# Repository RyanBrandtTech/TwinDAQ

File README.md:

# TwinDAQ
* An STM32-based two-channel analog I/O data acquisition system and development board

## Features
* Two analog inputs accessible with SMA connectors
* Two analog outputs accessible with SMA connectors
* Eight digital GPIO accessible via 0.1" female pin headers
* Two RGB LEDs for visual debugging
* Connector for SWD interfacing
* Connector for UART interfacing
* Micro-USB for 5V power and USB2.0 communications

### Dimensions and Images
40 mm x 60 mm

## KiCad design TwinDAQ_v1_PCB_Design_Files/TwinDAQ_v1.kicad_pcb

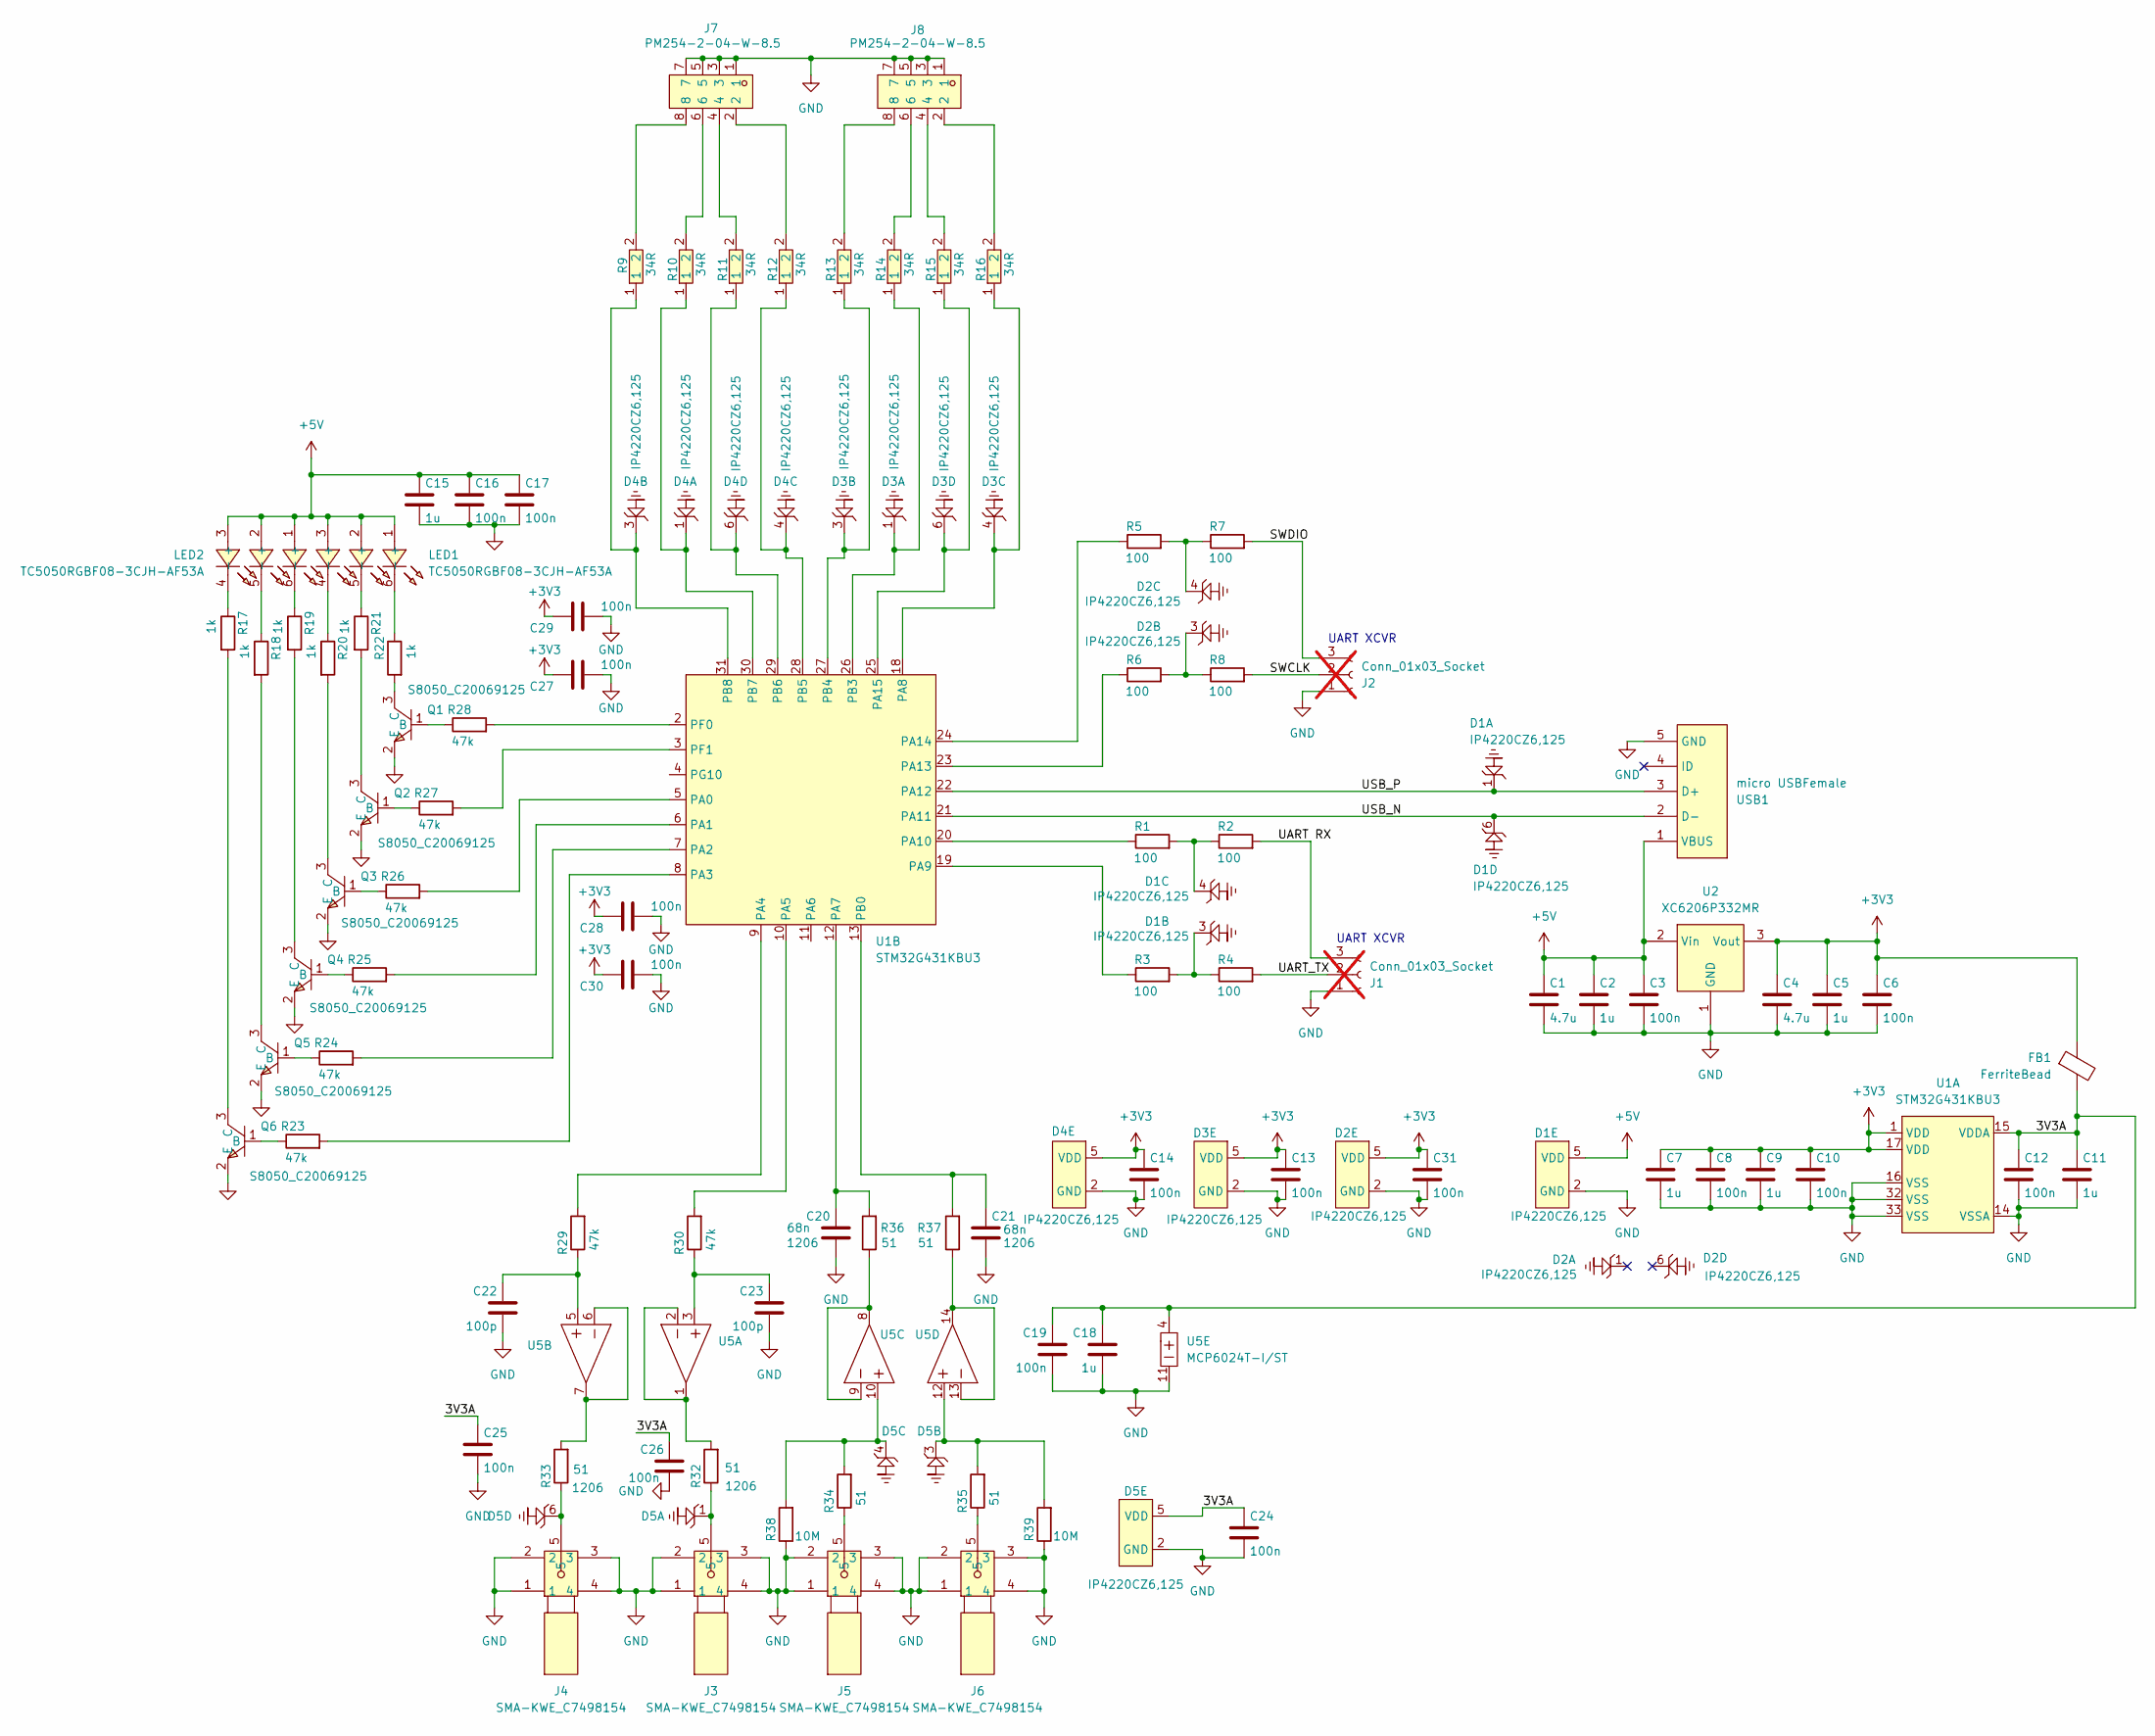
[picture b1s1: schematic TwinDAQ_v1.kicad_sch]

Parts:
C1, C4: 4.7u; C_0402_1005Metric_Pad0.74x0.62mm_HandSolder; LCSC Part C23733
C2, C5, C7, C9, C11, C15, C18: 1u; C_0402_1005Metric_Pad0.74x0.62mm_HandSolder; LCSC Part C14445
C3, C6, C8, C10, C12, C13, C14, C16, C17, C19, C24, C25, C26, C27, C28, C29, C30, C31: 100n; C_0402_1005Metric_Pad0.74x0.62mm_HandSolder; LCSC Part C1525
C20, C21: 68n; C1206; LCSC Part C77084
C22, C23: 100p; C0402; LCSC Part C1546
D1, D2, D3, D4, D5: IP4220CZ6,125; TSOP-6_L3.0-W1.5-P0.95-LS2.8-BR; LCSC Part C282546
FB1: FerriteBead; L_0603_1608Metric_Pad1.05x0.95mm_HandSolder; LCSC Part C1002
J1, J2: Conn_01x03_Socket; PinSocket_1x03_P2.54mm_Vertical; LCSC Part C541850; not fitted
J3, J4, J5, J6: SMA-KWE_C7498154; SMA-TH_SMA-KWE_C7498154; LCSC Part C7498154
J7, J8: PM254-2-04-W-8.5; HDR-TH_8P-P2.54-H-F-R2-C4-W8.5; LCSC Part C2897424
LED1, LED2: TC5050RGBF08-3CJH-AF53A; LED-SMD_6P-L5.0-W5.0-TL_TC5050RGBF08; LCSC Part C784540
Q1, Q2, Q3, Q4, Q5, Q6: S8050_C20069125; SOT-23-3_L2.9-W1.3-P1.90-LS2.3-BR; LCSC Part C20069125
R1, R2, R3, R4, R5, R6, R7, R8: 100; R_0402_1005Metric_Pad0.72x0.64mm_HandSolder; LCSC Part C25076
R9, R10, R11, R12, R13, R14, R15, R16: 34R; R0603; LCSC Part C25193
R17, R18, R19, R20, R21, R22: 1k; R0402; LCSC Part C11702
R23, R24, R25, R26, R27, R28, R29, R30: 47k; R0402; LCSC Part C25792
R32, R33: 51; R1206; LCSC Part C18019
R34, R35, R36, R37: 51; R0402; LCSC Part C25125
R38, R39: 10M; R0402; LCSC Part C26082
U1: STM32G431KBU3; QFN-32-1EP_5x5mm_P0.5mm_EP3.45x3.45mm; LCSC Part C1341901
U2: XC6206P332MR; SOT-23-3_L2.9-W1.6-P1.90-LS2.8-BR; LCSC Part C5446
U5: MCP6024T-I/ST; TSSOP-14_L5.0-W4.4-P0.65-LS6.5-BL; LCSC Part C480630
USB1: micro USBFemale; MICRO-USB-SMD_5P-P0.65-H-F_C10418; LCSC Part C10418

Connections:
+3V3: C4.1, C5.1, C6.1, C7.1, C8.1, C9.1, C10.1, C13.1, C14.1, C27.1, C28.1, C29.1, C30.1, C31.1, D2.5 (VDD), D3.5 (VDD), D4.5 (VDD), FB1.1, U1.1 (VDD), U1.17 (VDD), U2.3 (Vout)
+5V: C1.1, C2.1, C3.1, C15.1, C16.1, C17.1, D1.5 (VDD), LED1.1 (+), LED1.2 (+), LED1.3 (+), LED2.1 (+), LED2.2 (+), LED2.3 (+), U2.2 (Vin), USB1.1 (VBUS)
/3V3A: C11.1, C12.1, C18.1, C19.1, C24.1, C25.1, C26.1, D5.5 (VDD), FB1.2, U1.15 (VDDA), U5.4
/SWCLK: J2.2, R8.2
/SWDIO: J2.3, R7.2
/UART RX: J1.3, R2.2
/UART_TX: J1.2, R4.2
/USB_N: D1.6, U1.21 (PA11), USB1.2 (D-)
/USB_P: D1.1, U1.22 (PA12), USB1.3 (D+)
GND: C1.2, C2.2, C3.2, C4.2, C5.2, C6.2, C7.2, C8.2, C9.2, C10.2, C11.2, C12.2, C13.2, C14.2, C15.2, C16.2, C17.2, C18.2, C19.2, C20.2, C21.2, C22.2, C23.2, C24.2, C25.2, C26.2, C27.2, C28.2, C29.2, C30.2, C31.2, D1.2 (GND), D2.2 (GND), D3.2 (GND), D4.2 (GND), D5.2 (GND), J1.1, J2.1, J3.1, J3.2, J3.3, J3.4, J4.1, J4.2, J4.3, J4.4, J5.1, J5.2, J5.3, J5.4, J6.1, J6.2, J6.3, J6.4, J7.1, J7.3, J7.5, J7.7, J8.1, J8.3, J8.5, J8.7, Q1.2 (E), Q2.2 (E), Q3.2 (E), Q4.2 (E), Q5.2 (E), Q6.2 (E), R38.1, R39.1, U1.14 (VSSA), U1.16 (VSS), U1.32 (VSS), U1.33 (VSS), U2.1 (GND), U5.11, USB1.5 (GND)
unnamed: C22.1, R29.1, U5.5
unnamed: C23.1, R30.1, U5.3
unnamed: D1.3, R3.2, R4.1
unnamed: D1.4, R1.2, R2.1
unnamed: D2.3, R6.2, R8.1
unnamed: D2.4, R5.2, R7.1
unnamed: D3.1, R14.1, U1.26 (PB3)
unnamed: D3.3, R13.1, U1.27 (PB4)
unnamed: D3.4, R16.1, U1.18 (PA8)
unnamed: D3.6, R15.1, U1.25 (PA15)
unnamed: D4.1, R10.1, U1.30 (PB7)
unnamed: D4.3, R9.1, U1.31 (PB8)
unnamed: D4.4, R12.1, U1.28 (PB5)
unnamed: D4.6, R11.1, U1.29 (PB6)
unnamed: D5.1, J3.5, R32.1
unnamed: D5.3, R35.2, R39.2, U5.12
unnamed: D5.4, R34.2, R38.2, U5.10
unnamed: D5.6, J4.5, R33.1
unnamed: J5.5, R34.1
unnamed: J6.5, R35.1
unnamed: J7.2, R12.2
unnamed: J7.4, R11.2
unnamed: J7.6, R10.2
unnamed: J7.8, R9.2
unnamed: J8.2, R16.2
unnamed: J8.4, R15.2
unnamed: J8.6, R14.2
unnamed: J8.8, R13.2
unnamed: LED1.4 (-), R20.1
unnamed: LED1.5 (-), R21.1
unnamed: LED1.6 (-), R22.1
unnamed: LED2.4 (-), R17.1
unnamed: LED2.5 (-), R18.1
unnamed: LED2.6 (-), R19.1
unnamed: Q1.1 (B), R28.1
unnamed: Q1.3 (C), R22.2
unnamed: Q2.1 (B), R27.1
unnamed: Q2.3 (C), R21.2
unnamed: Q3.1 (B), R26.1
unnamed: Q3.3 (C), R20.2
unnamed: Q4.1 (B), R25.1
unnamed: Q4.3 (C), R19.2
unnamed: Q5.1 (B), R24.1
unnamed: Q5.3 (C), R18.2
unnamed: Q6.1 (B), R23.1
unnamed: Q6.3 (C), R17.2
unnamed: R32.2, U5.1, U5.2
unnamed: R33.2, U5.6, U5.7
unnamed: R36.1, U5.8, U5.9
unnamed: R37.1, U5.13, U5.14
unnamed: R26.2, U1.5 (PA0)
unnamed: R25.2, U1.6 (PA1)
unnamed: R24.2, U1.7 (PA2)
unnamed: R23.2, U1.8 (PA3)
unnamed: R29.2, U1.9 (PA4)
unnamed: R30.2, U1.10 (PA5)
unnamed: C20.1, R36.2, U1.12 (PA7)
unnamed: R3.1, U1.19 (PA9)
unnamed: R1.1, U1.20 (PA10)
unnamed: R6.1, U1.23 (PA13)
unnamed: R5.1, U1.24 (PA14)
unnamed: C21.1, R37.2, U1.13 (PB0)
unnamed: R28.2, U1.2 (PF0)
unnamed: R27.2, U1.3 (PF1)

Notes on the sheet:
UART XCVR

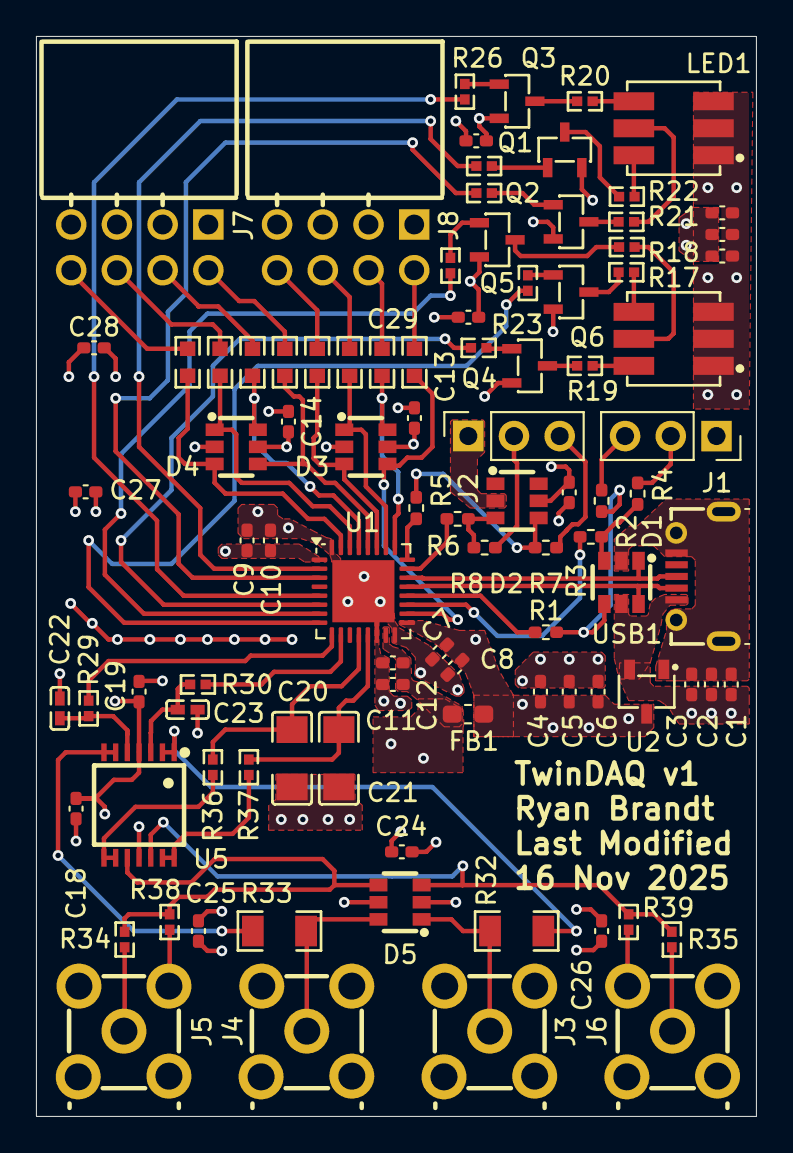
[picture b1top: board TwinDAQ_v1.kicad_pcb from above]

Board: 4 copper layers, 40.0 x 60.0 mm, 95 parts (0 on the bottom side), 74 nets.

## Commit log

2025-11-17 Add PCB Design Files for v1 Order
2025-11-18 Add Images of PCB Design for Documentation
2025-11-18 Add README.md
